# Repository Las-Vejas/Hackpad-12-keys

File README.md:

# Micro Macro Pad  
  
This is my 12 key macro pad made for Hackpad.

## Features  
Has 12 switches  
An 0.91 OLED screen  
Has 12 SK6812MINI Leds
  
## Firmware  
I made it with RMK and I hope it'll work.

## PCB
I made the PCB in KiCad and had to reroute it like 10 times.

## CAD model
I made it in Autodesk Fusion, it has a top and bottom part.

## Schematic

## BOM

- 16x Cherry MX switches
- 16x SK6812MINI Leds
- 1x 0.91 inch OLED
- 16x 1N4148 diodes
- 1x XIAO RP2040
- 16x Blank DSA Keycaps
- 4x M3x16 Bolt
- 4x M3 Heatset

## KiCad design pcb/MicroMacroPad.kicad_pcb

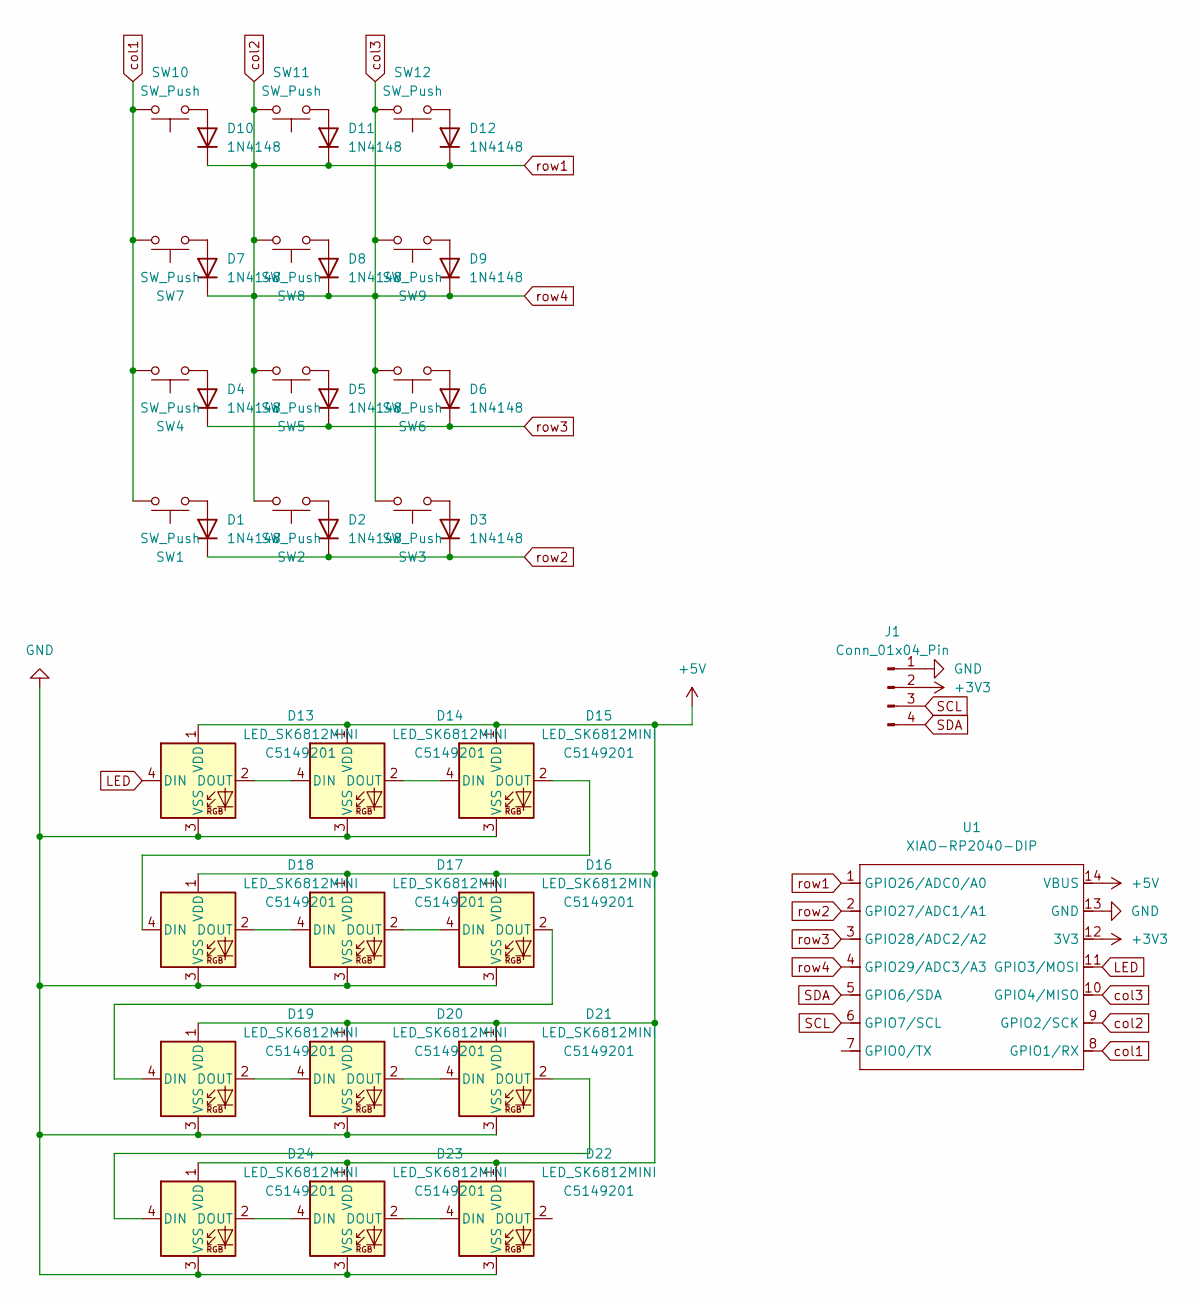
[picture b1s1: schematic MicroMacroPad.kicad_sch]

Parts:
D1, D2, D3, D4, D5, D6, D7, D8, D9, D10, D11, D12: 1N4148; D_DO-35_SOD27_P7.62mm_Horizontal
D13, D14, D15, D16, D17, D18, D19, D20, D21, D22, D23, D24: LED_SK6812MINI; LCSC C5149201
J1: Conn_01x04_Pin; SSD1306-0.91-OLED-4pin-128x32
SW1, SW2, SW3, SW4, SW5, SW6, SW7, SW8, SW9, SW10, SW11, SW12: SW_Push; SW_Cherry_MX_1.00u_PCB
U1: XIAO-RP2040-DIP

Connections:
+3V3: J1.2, U1.12 (3V3)
+5V: D13.1 (VDD), D14.1 (VDD), D15.1 (VDD), D16.1 (VDD), D17.1 (VDD), D18.1 (VDD), D19.1 (VDD), D20.1 (VDD), D21.1 (VDD), D22.1 (VDD), D23.1 (VDD), D24.1 (VDD), U1.14 (VBUS)
GND: D13.3 (VSS), D14.3 (VSS), D15.3 (VSS), D16.3 (VSS), D17.3 (VSS), D18.3 (VSS), D19.3 (VSS), D20.3 (VSS), D21.3 (VSS), D22.3 (VSS), D23.3 (VSS), D24.3 (VSS), J1.1, U1.13 (GND)
LED: D13.4 (DIN), U1.11 (GPIO3/MOSI)
unnamed: D1.2 (A), SW1.1
unnamed: D2.2 (A), SW2.1
unnamed: D3.2 (A), SW3.1
unnamed: D4.2 (A), SW4.1
unnamed: D5.2 (A), SW5.1
unnamed: D6.2 (A), SW6.1
unnamed: D7.2 (A), SW7.1
unnamed: D8.2 (A), SW8.1
unnamed: D9.2 (A), SW9.1
unnamed: D10.2 (A), SW10.1
unnamed: D11.2 (A), SW11.1
unnamed: D12.2 (A), SW12.1
unnamed: D13.2 (DOUT), D14.4 (DIN)
unnamed: D14.2 (DOUT), D15.4 (DIN)
unnamed: D15.2 (DOUT), D18.4 (DIN)
unnamed: D16.4 (DIN), D17.2 (DOUT)
unnamed: D16.2 (DOUT), D19.4 (DIN)
unnamed: D17.4 (DIN), D18.2 (DOUT)
unnamed: D19.2 (DOUT), D20.4 (DIN)
unnamed: D20.2 (DOUT), D21.4 (DIN)
unnamed: D21.2 (DOUT), D24.4 (DIN)
unnamed: D22.4 (DIN), D23.2 (DOUT)
unnamed: D23.4 (DIN), D24.2 (DOUT)
SCL: J1.3, U1.6 (GPIO7/SCL)
SDA: J1.4, U1.5 (GPIO6/SDA)
col1: SW1.2, SW4.2, SW7.2, SW10.2, U1.8 (GPIO1/RX)
col2: D7.1 (K), D8.1 (K), D9.1 (K), D10.1 (K), D11.1 (K), D12.1 (K), SW2.2, SW3.2, SW5.2, SW6.2, SW8.2, SW9.2, SW11.2, SW12.2, U1.1 (GPIO26/ADC0/A0), U1.4 (GPIO29/ADC3/A3), U1.9 (GPIO2/SCK), U1.10 (GPIO4/MISO)
row2: D1.1 (K), D2.1 (K), D3.1 (K), U1.2 (GPIO27/ADC1/A1)
row3: D4.1 (K), D5.1 (K), D6.1 (K), U1.3 (GPIO28/ADC2/A2)

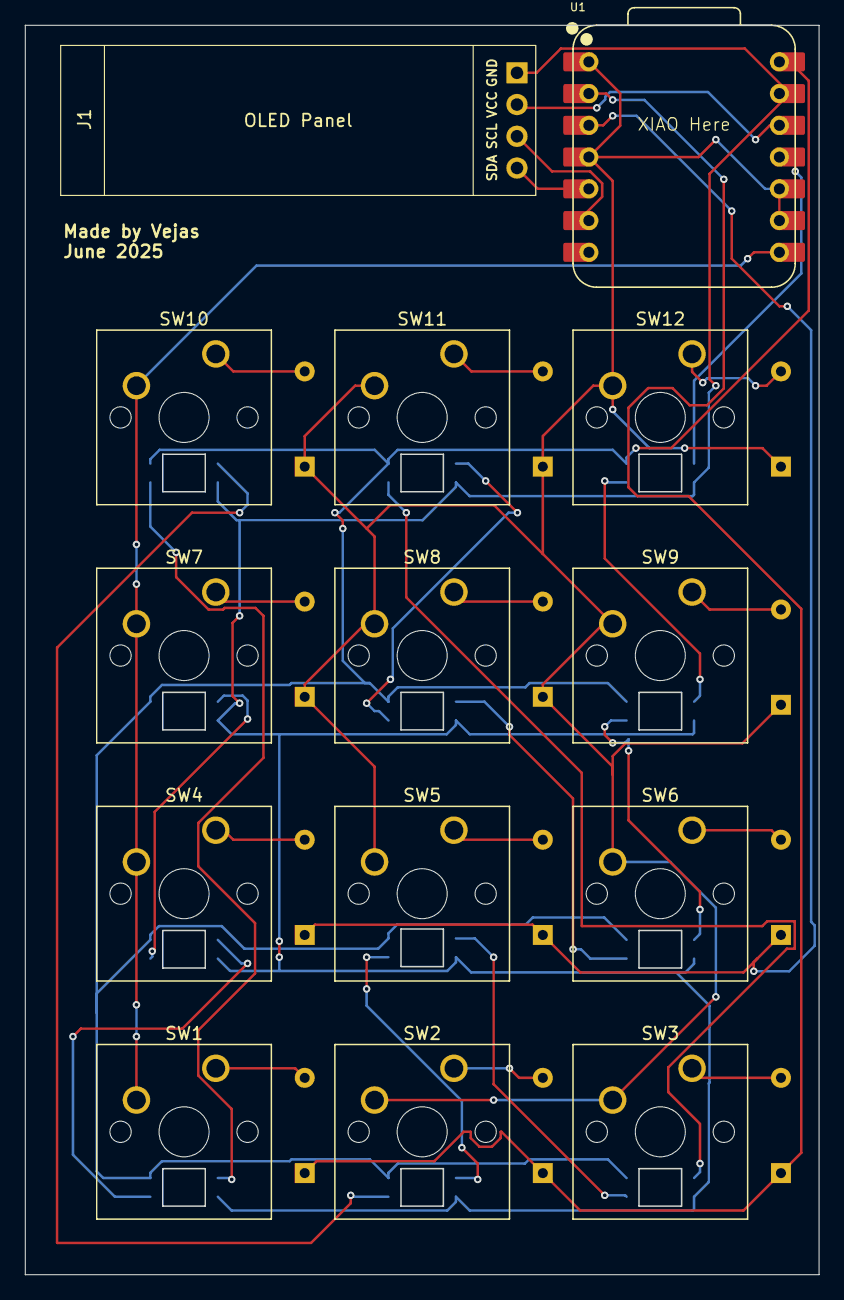
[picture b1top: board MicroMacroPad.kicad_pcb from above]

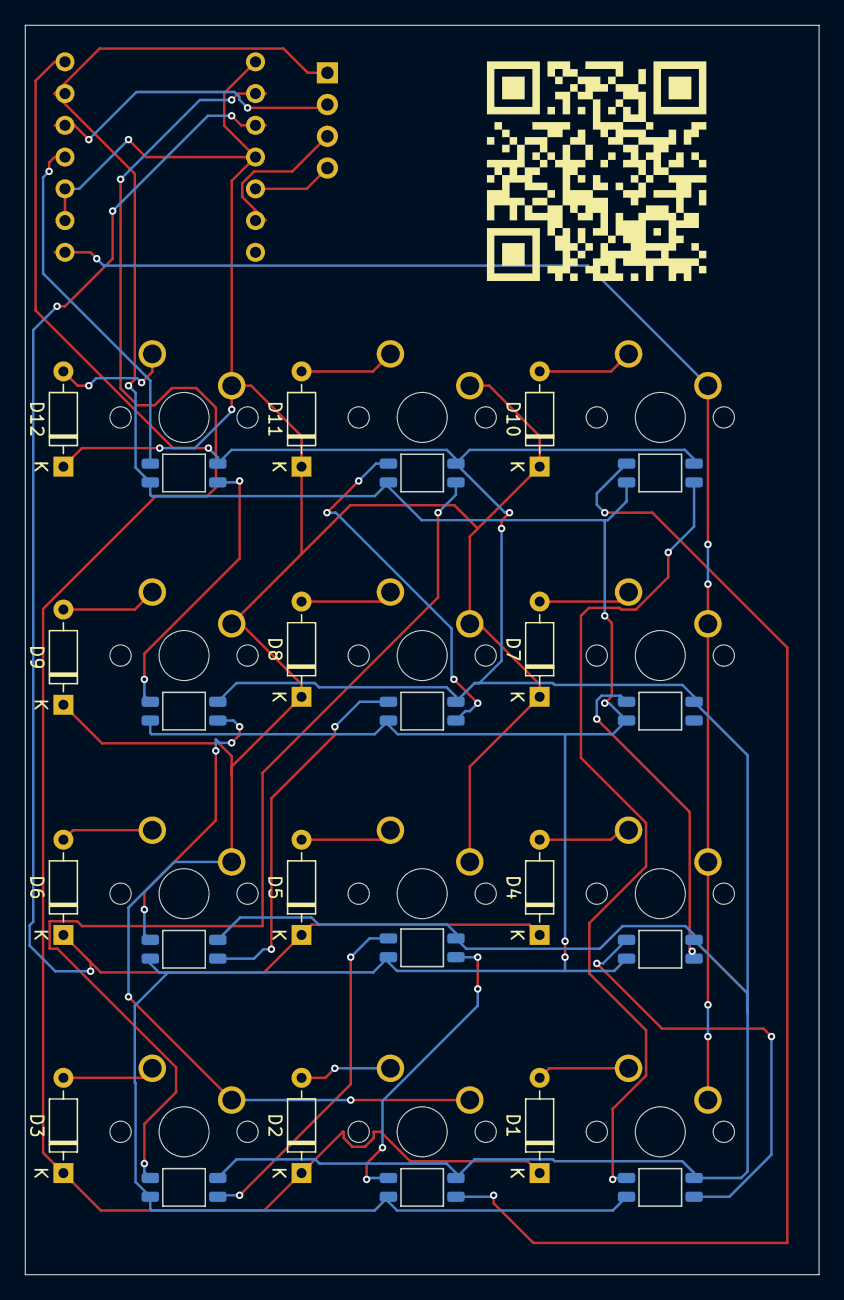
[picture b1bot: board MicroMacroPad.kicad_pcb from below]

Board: 2 copper layers, 63.4 x 99.9 mm, 38 parts (24 on the bottom side), 33 nets.

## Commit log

2025-06-29 added schem images
2025-06-29 Added firmware
2025-06-29 Rename firmware_uf2.zip to firmware/firmware_uf2.zip
2025-06-30 Rename RMK_Keyboard.uf2 to firmware/RMK_Keyboard.uf2
2025-06-30 Rename keyboard.toml to keyboard.toml
2025-06-30 Rename vial.json to vial.json
2025-06-30 Rename RMK_Keyboard.uf2 to production/RMK_Keyboard.uf2
2025-07-01 V2 upload
